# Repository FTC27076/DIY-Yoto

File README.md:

# DIY Yoto

A screen-free, kid-friendly audio player in the style of a Yoto. Put a card on top and it plays that card's stories or songs. It runs fully offline: no Wi-Fi, no app, no account. All audio lives on a micro SD card, and any 13.56 MHz RFID card or NFC sticker can become a card.

## Features

- Tap a card to play, lift it to pause, put it back to resume where it stopped
- Each card remembers which track it was on
- Two knobs: volume (press to pause) and track skip (press to restart the track)
- Volume cap for small ears
- Rechargeable LiPo with USB-C charging; play while charging
- Deep sleep after 5 minutes idle, wake with either knob
- Low-battery warning and safe shutdown

## Hardware

| Part | What it does |
|---|---|
| ESP32-S3-WROOM-1 (SMD) | Main controller |
| RC522 RFID reader | Reads the cards |
| Adafruit MAX98357A (#3006) | I2S amplifier, drives a 4–8 Ω 3 W speaker |
| Adafruit micro SD breakout (#4682) | Audio storage, 4-bit SDIO |
| TP4056 USB-C module (with protection) | Charges and protects the battery |
| MT3608 boost module | 5 V for the amp (set to 5.0 V before connecting!) |
| MCP1825S-3302E/AB (TO-220) | 3.3 V regulator for the logic |
| 2× EC11 rotary encoders | Volume and track controls |
| USB-C (J16) | Programming and Serial Monitor only |
| 3.7 V 2000 mAh LiPo (Adafruit #2011) | Power |

Everything except the ESP32 module is through-hole or a module on headers, so it's hand-solderable.
## BILL OF MATERIALS

Costs are in USD for one player. Most unit prices are estimates, so check them in each cart.

| Item | Qty | Supplier | Cost/item | Total Cost | link |
|---|---:|---|---:|---:|---|
| U2 – ESP32-S3-WROOM-1-N8R8 module (Espressif) | 1 | DigiKey | $4.50 | $4.50 | [link](https://www.digikey.ca/en/products/detail/espressif-systems/ESP32-S3-WROOM-1-N8R8/15295891) |
| U1 – MCP1825S-3302E/AB 3.3V LDO, TO-220 (Microchip) | 1 | DigiKey | $1.75 | $1.75 | [link](https://www.digikey.ca/en/products/result?keywords=MCP1825S-3302E%2FAB) |
| R1, R2 – 100k 1/4W resistor (Stackpole CF14JT100K, cut tape) | 2 | DigiKey | $0.10 | $0.20 | [link](https://www.digikey.ca/en/products/result?keywords=CF14JT100K) |
| R3–R8 – 10k 1/4W resistor (Stackpole CF14JT10K0, cut tape) | 6 | DigiKey | $0.10 | $0.60 | [link](https://www.digikey.ca/en/products/result?keywords=CF14JT10K0) |
| R9, R10 – 5.1k 1/4W resistor (Stackpole CF14JT5K10, cut tape) | 2 | DigiKey | $0.10 | $0.20 | [link](https://www.digikey.ca/en/products/detail/stackpole-electronics-inc/CF14JT5K10/1830367) |
| C1, C5 – 100µF 16V electrolytic (Panasonic EEU-FR1C101) | 2 | DigiKey | $0.40 | $0.80 | [link](https://www.digikey.ca/en/products/detail/panasonic-industry/EEU-FR1C101/2433525) |
| C2, C3, C9 – 10µF 25V ceramic, 5mm pitch (TDK FG28X5R1E106MRT06) | 3 | LCSC / JLC | $0.20 | $0.60 | [link](https://www.lcsc.com/product-detail/C1620216.html) |
| C4, C6, C7, C10 – 100nF 50V ceramic (KNSCHA 178MU0006) | 4 | LCSC / JLC | $0.03 | $0.12 | [link](https://www.lcsc.com/product-detail/C5632430.html) |
| C8 – 1µF 50V ceramic (KNSCHA 178MU0010) | 1 | LCSC / JLC | $0.05 | $0.05 | [link](https://www.lcsc.com/product-detail/C5632434.html) |
| SW2, SW3 – 6x6mm tactile switch, reset/boot (Omron B3F-1000) | 2 | DigiKey | $0.35 | $0.70 | [link](https://www.digikey.ca/en/products/detail/omron-electronics-inc-emc-div/B3F-1000/33150) |
| SW4, SW5 – rotary encoder with switch (Alps EC11E15244G1) | 2 | LCSC / JLC | $1.50 | $3.00 | [link](https://www.lcsc.com/product-detail/C370970.html) |
| J16 – USB-C receptacle, 16-pin (HRO TYPE-C-31-M-12) | 1 | LCSC / JLC | $0.25 | $0.25 | [link](https://www.lcsc.com/product-detail/C165948.html) |
| J3 – JST-PH 2-pin side-entry socket, battery (JST S2B-PH-K-S) | 1 | LCSC / JLC | $0.10 | $0.10 | [link](https://www.lcsc.com/product-detail/C173752.html) |
| J7 – JST-XH 2-pin socket, power switch (JST B2B-XH-A) | 1 | LCSC / JLC | $0.05 | $0.05 | [link](https://www.lcsc.com/product-detail/C158012.html) |
| MOD1 – 1x8 2.54mm female header (BOOMELE) | 1 | LCSC / JLC | $0.10 | $0.10 | [link](https://www.lcsc.com/product-detail/C27438.html) |
| J12 (M1) – TP4056 USB-C charger module with protection (pack of 5) | 1 | Amazon | $8.00 | $8.00 | [link](https://www.amazon.ca/s?k=TP4056+type-c+protection+module) |
| J13 (M2) – MT3608 boost module (pack of 5) | 1 | Amazon | $8.00 | $8.00 | [link](https://www.amazon.ca/s?k=MT3608+boost+module) |
| J14 (M3) – Adafruit MAX98357A I2S amp breakout (3006) | 1 | DigiKey | $5.95 | $5.95 | [link](https://www.digikey.ca/en/products/detail/adafruit-industries-llc/3006/6058477) |
| J15 (M4) – Adafruit micro SD SPI/SDIO breakout (4682) | 1 | DigiKey | $3.50 | $3.50 | [link](https://www.digikey.ca/en/products/detail/adafruit-industries-llc/4682/12822319) |
| MOD1 – RC522 RFID reader kit with card + fob (ProtoSupplies) | 1 | ProtoSupplies | $2.59 | $2.59 | [link](https://protosupplies.com/product/mfrc522-rfid-reader-key-card-and-key-ring/) |
| Header pins for M1/M2 – 1x40 break-away male header (BOOMELE) | 1 | LCSC / JLC | $0.15 | $0.15 | [link](https://www.lcsc.com/product-detail/C2337.html) |
| LiPo battery 3.7V 2000mAh with JST-PH (Adafruit 2011) | 1 | DigiKey | $12.50 | $12.50 | [link](https://www.digikey.ca/en/products/detail/adafruit-industries-llc/2011/6612469) |
| Speaker 40mm 4Ω 3W (Adafruit 3968) | 1 | DigiKey | $4.95 | $4.95 | [link](https://www.digikey.ca/en/products/detail/adafruit-industries-llc/3968/9745251) |
| Power switch – SPDT panel toggle 5A (E-Switch 100SP1T1B1M2QEH) | 1 | DigiKey | $4.50 | $4.50 | [link](https://www.digikey.ca/en/products/detail/e-switch/100SP1T1B1M2QEH/378821) |
| RFID cards – MIFARE Classic 1K (Adafruit 359) | 5 | DigiKey | $1.95 | $9.75 | [link](https://www.digikey.ca/en/products/detail/adafruit-industries-llc/359/5353589) |
| micro SD card 16–32GB (SanDisk / Samsung) | 1 | Amazon | $8.00 | $8.00 | [link](https://www.amazon.ca/s?k=sandisk+32gb+microsd) |
| Optional – JST-XH plug housing for J7 (JST XHP-2) | 0 | DigiKey | $0.10 | $0.00 | [link](https://www.digikey.ca/en/products/detail/jst-sales-america-inc/XHP-2/555485) |
| Optional – JST-XH crimp contacts (JST SXH-001T-P0.6, cut tape) | 0 | DigiKey | $0.10 | $0.00 | [link](https://www.digikey.ca/en/products/detail/jst-sales-america-inc/SXH-001T-P0.6/455-1135-1-ND/527370) |
| Parts subtotal | | | | $80.91 | |
| Tax (Ontario HST 13%) | | | | $13.77 | |
| **Grand total (USD)** | | | | **~$119.68** | |

### Pin map

| Function | GPIO |
|---|---|
| I2S BCLK / LRC / DIN | 5 / 6 / 7 |
| Amp enable (SD_MODE) | 8 |
| RC522 RST / SS / MOSI / SCK / MISO | 9 / 10 / 11 / 12 / 13 |
| SD CMD / CLK / D0 / D1 / D2 / D3 | 14 / 39 / 40 / 41 / 42 / 21 |
| Volume encoder A / B / push | 15 / 16 / 17 |
| Track encoder A / B / push | 18 / 4 / 2 |
| Battery sense (100k/100k divider) | 1 |
| USB D− / D+ | 19 / 20 |

## Repository contents

| Path | What's in it |
|---|---|
| `DiyYoto/DiyYoto.ino` | Arduino firmware |
| `DiyYoto/README.md` | Full firmware setup, SD card layout, controls and troubleshooting |
| `DiyYoto.pretty/` | Custom KiCad footprints for the four modules |
| `make_footprints.py` | Regenerates those footprints |

## Quick start

1. **Build the board.** Order the PCB, solder the parts, and set the MT3608 to 5.0 V with a multimeter *before* plugging in the amp.
2. **Flash the firmware.** In Arduino IDE 2, install the ESP32 core plus the MFRC522 and ESP32-audioI2S libraries. Set Board to *ESP32S3 Dev Module*, USB CDC On Boot to *Enabled*, and PSRAM to match your module. Switch the player on, plug USB into J16, hold BOOT, tap RESET, release BOOT, then upload.
3. **Prepare the SD card.** Format it FAT32 and create a `/cards` folder.
4. **Add a card.** Tap a blank card. The player creates `/cards/<card UID>/`. Copy MP3s into that folder (they play in alphabetical order), put the SD card back, and tap again.

## Images of final design

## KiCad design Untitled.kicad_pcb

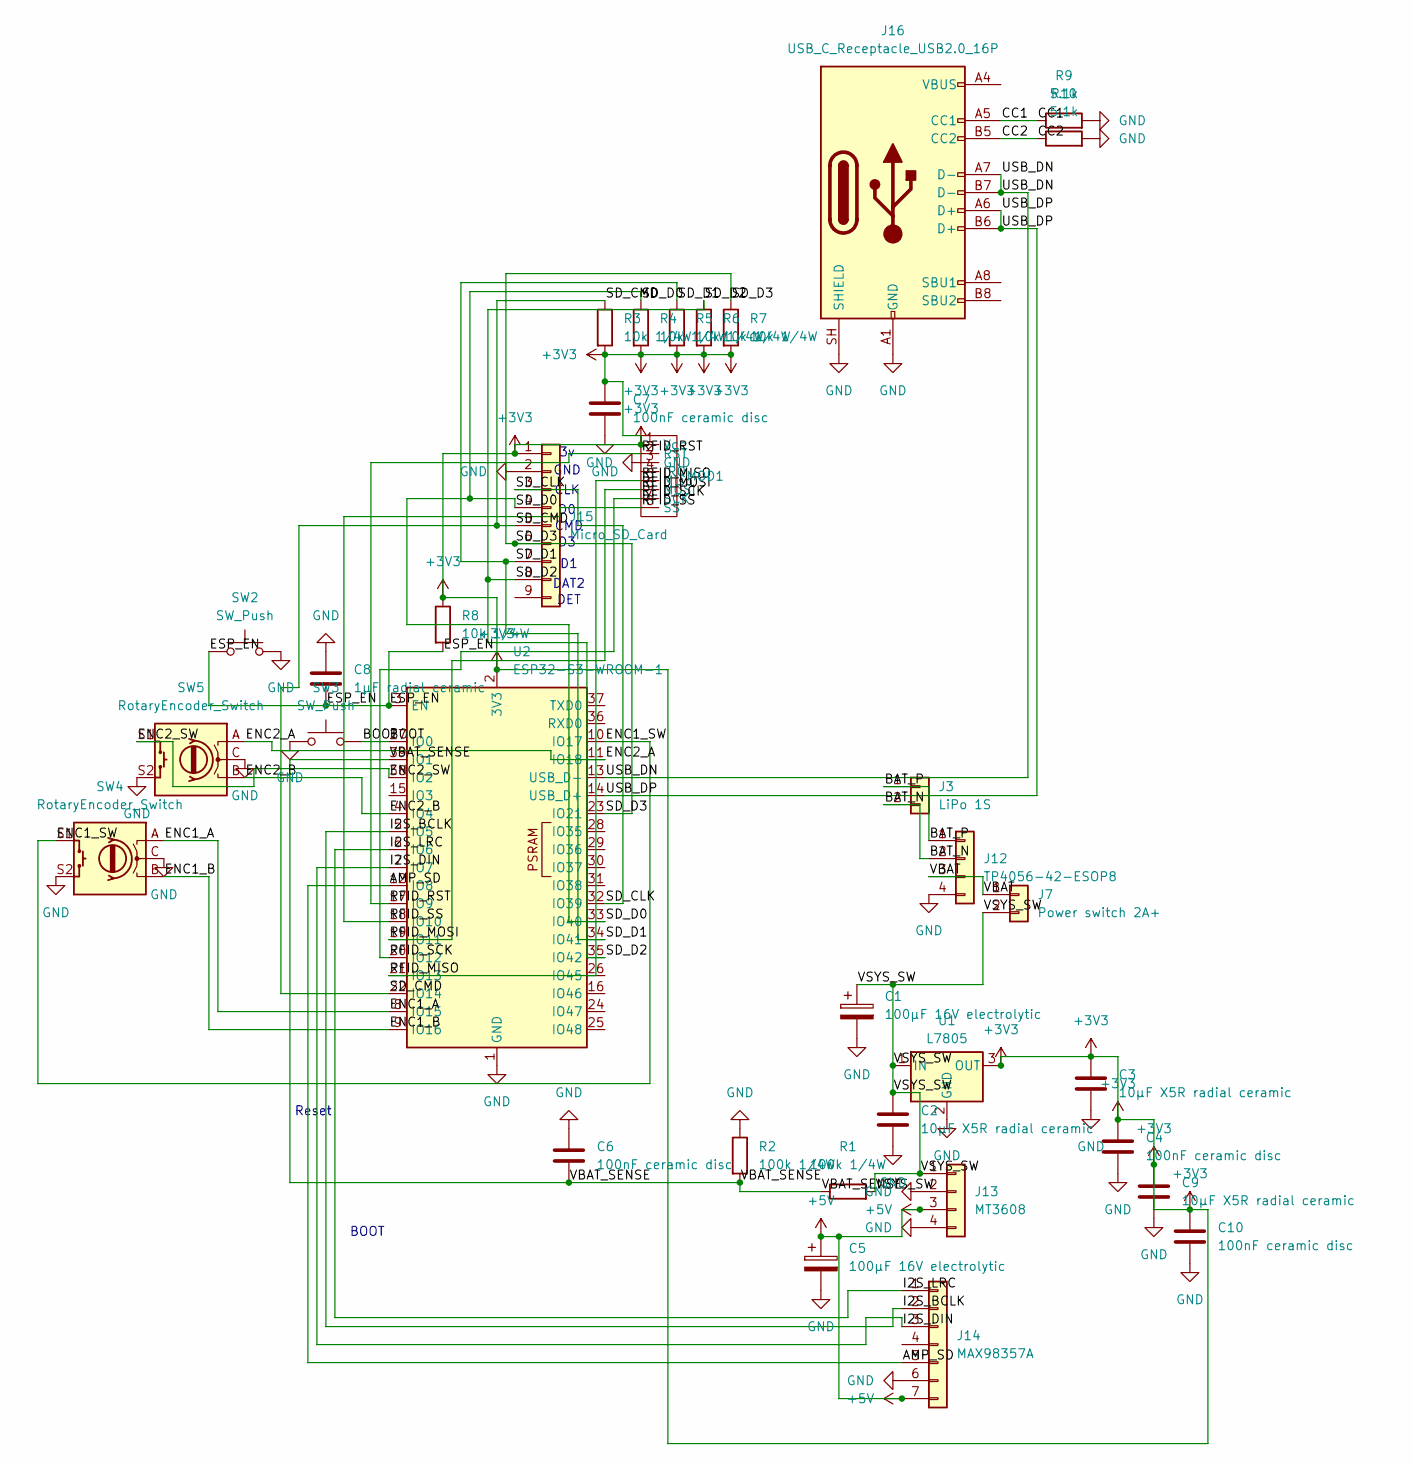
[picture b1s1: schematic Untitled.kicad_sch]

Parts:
C1, C5: 100µF 16V electrolytic; CP_Radial_D6.3mm_P2.50mm
C2, C3, C9: 10µF X5R radial ceramic; C_Disc_D5.0mm_W2.5mm_P2.50mm
C4, C6, C7, C10: 100nF ceramic disc; C_Disc_D3.0mm_W1.6mm_P2.50mm
C8: 1µF radial ceramic; C_Disc_D3.0mm_W1.6mm_P2.50mm
J3: LiPo 1S; JST_PH_S2B-PH-K_1x02_P2.00mm_Horizontal
J7: Power switch 2A+; JST_XH_B2B-XH-A_1x02_P2.50mm_Vertical
J12: TP4056-42-ESOP8; TP4056_USBC_Protected_Module
J13: MT3608; MT3608_Boost_Module
J14: MAX98357A; Adafruit_MAX98357A_3006
J15: Micro_SD_Card; Adafruit_MicroSD_SDIO_4682
J16: USB_C_Receptacle_USB2.0_16P; USB_C_Receptacle_HRO_TYPE-C-31-M-12
MOD1: PinSocket_1x08_P2.54mm_Vertical
R1, R2: 100k 1/4W; R_Axial_DIN0207_L6.3mm_D2.5mm_P10.16mm_Horizontal
R3, R4, R5, R6, R7, R8: 10k 1/4W; R_Axial_DIN0207_L6.3mm_D2.5mm_P10.16mm_Horizontal
R9, R10: 5.1k; R_Axial_DIN0207_L6.3mm_D2.5mm_P10.16mm_Horizontal
SW2, SW3: SW_Push; SW_PUSH_6mm
SW4, SW5: RotaryEncoder_Switch; RotaryEncoder_Alps_EC11E-Switch_Vertical_H20mm_MountingHoles
U1: L7805; TO-220-3_Vertical
U2: ESP32-S3-WROOM-1; ESP32-S3-WROOM-1ThermalVia0.3

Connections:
+3V3: C3.1, C4.1, C7.1, C9.1, C10.1, J15.1, MOD1.1 (Vcc), R3.2, R4.2, R5.2, R6.2, R7.2, R8.1, U1.3 (OUT), U2.2 (3V3)
+5V: C5.1, J13.3, J14.7
/AMP_SD: J14.5, U2.12 (IO8)
/BAT_N: J3.2, J12.2
/BAT_P: J3.1, J12.1
/BOOT: SW3.2, U2.27 (IO0)
/CC1: J16.A5 (CC1), R9.1
/CC2: J16.B5 (CC2), R10.1
/ENC1_A: SW4.A, U2.8 (IO15)
/ENC1_B: SW4.B, U2.9 (IO16)
/ENC1_SW: SW4.S1, U2.10 (IO17)
/ENC2_A: SW5.A, U2.11 (IO18)
/ENC2_B: SW5.B, U2.4 (IO4)
/ENC2_SW: SW5.S1, U2.38 (IO2)
/ESP_EN: C8.2, R8.2, SW2.1, U2.3 (EN)
/I2S_BCLK: J14.2, U2.5 (IO5)
/I2S_DIN: J14.3, U2.7 (IO7)
/I2S_LRC: J14.1, U2.6 (IO6)
/RFID_MISO: MOD1.5 (Miso), U2.21 (IO13)
/RFID_MOSI: MOD1.6 (MOSI), U2.19 (IO11)
/RFID_RST: MOD1.2 (RST), U2.17 (IO9)
/RFID_SCK: MOD1.7 (SCK), U2.20 (IO12)
/RFID_SS: MOD1.8 (SS), U2.18 (IO10)
/SD_CLK: J15.3, U2.32 (IO39)
/SD_CMD: J15.5, R3.1, U2.22 (IO14)
/SD_D0: J15.4, R4.1, U2.33 (IO40)
/SD_D1: J15.7, R5.1, U2.34 (IO41)
/SD_D2: J15.8, R6.1, U2.35 (IO42)
/SD_D3: J15.6, R7.1, U2.23 (IO21)
/USB_DN: J16.A7 (D-), J16.B7 (D-), U2.13 (USB_D-)
/USB_DP: J16.A6 (D+), J16.B6 (D+), U2.14 (USB_D+)
/VBAT: J7.1, J12.3
/VBAT_SENSE: C6.2, R1.1, R2.2, U2.39 (IO1)
/VSYS_SW: C1.1, C2.1, J7.2, J13.1, R1.2, U1.1 (IN)
GND: C1.2, C2.2, C3.2, C4.2, C5.2, C6.1, C7.2, C8.1, C9.2, C10.2, J12.4, J13.2, J13.4, J14.6, J15.2, J16.A1 (GND), J16.A12 (GND), J16.B1 (GND), J16.B12 (GND), J16.SH (SHIELD), MOD1.3 (GND), R2.1, R9.2, R10.2, SW2.2, SW3.1, SW4.C, SW4.S2, SW5.C, SW5.S2, U1.2 (GND), U2.1 (GND), U2.40 (GND), U2.41 (GND)
unnamed: J16.A4 (VBUS), J16.A9 (VBUS), J16.B4 (VBUS), J16.B9 (VBUS)

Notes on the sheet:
Reset
BOOT
DAT2
GND
CMD
CLK
DET

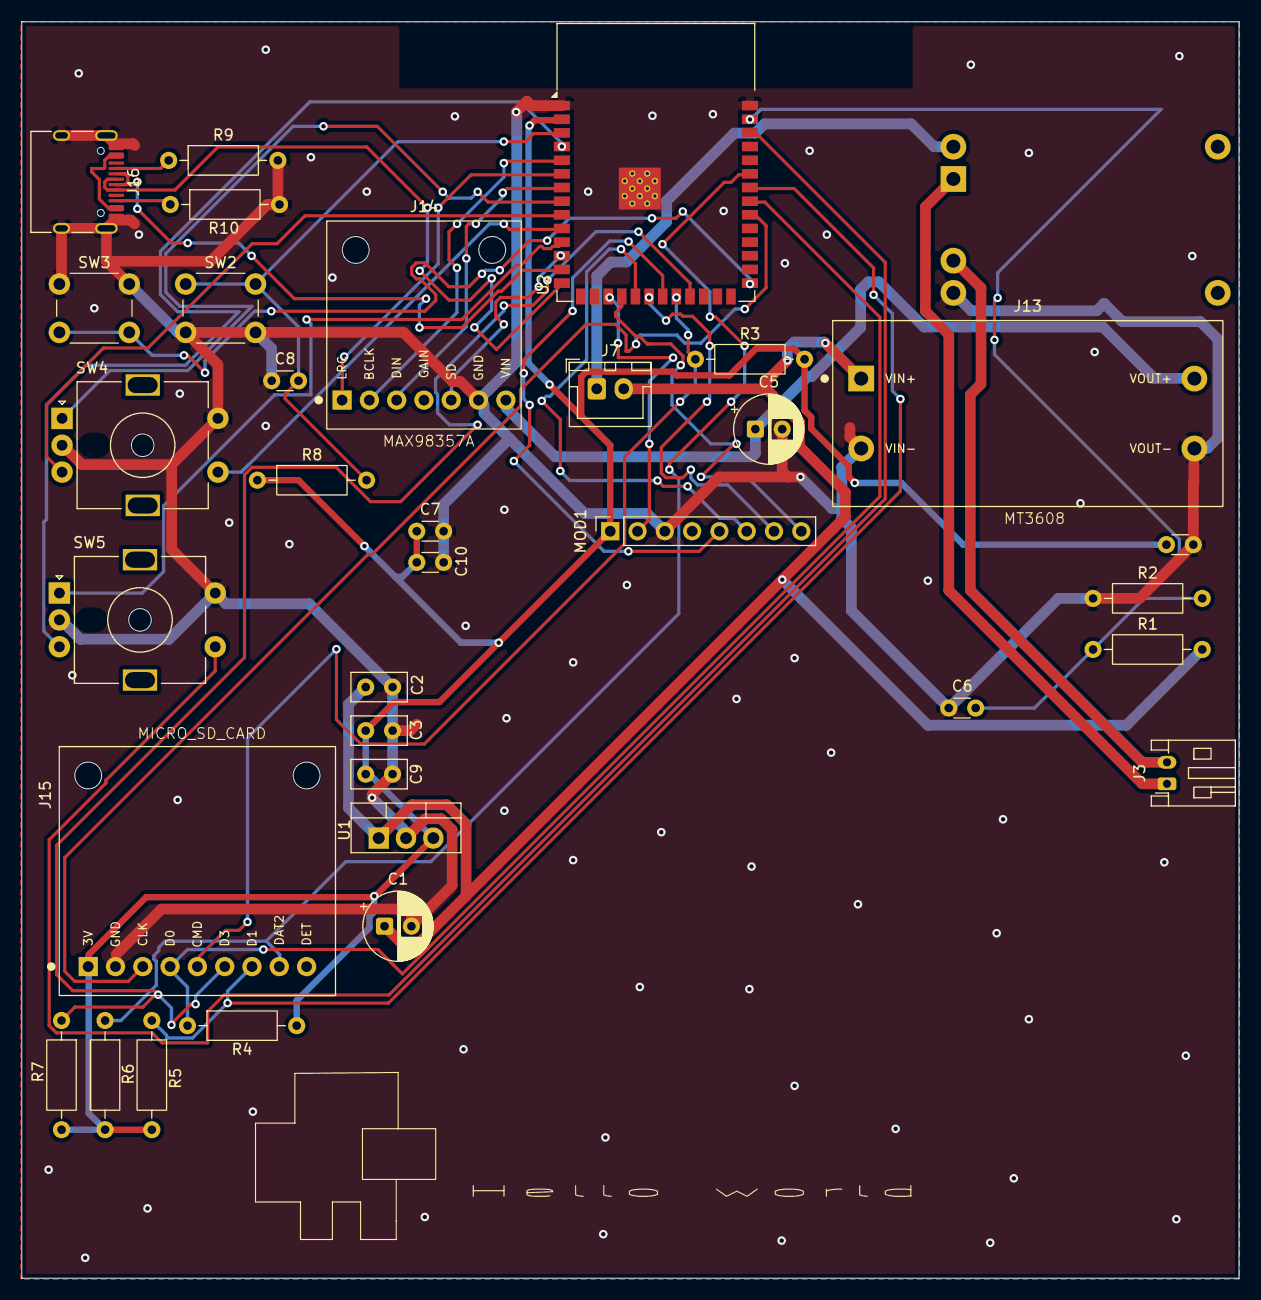
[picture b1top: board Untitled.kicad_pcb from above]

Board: 2 copper layers, 113.2 x 116.9 mm, 34 parts (1 on the bottom side), 36 nets.

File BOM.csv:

Item,Qty,Supplier,Cost/item,Total Cost,link
U2 – ESP32-S3-WROOM-1-N8R8 module (Espressif),1,DigiKey,$4.50,$4.50,https://www.digikey.ca/en/products/detail/espressif-systems/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
"U1 – MCP1825S-3302E/AB 3.3V LDO, TO-220 (Microchip)",1,DigiKey,$1.75,$1.75,https://www.digikey.ca/en/products/result?keywords=MCP1825S-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
"R1, R2 – 100k 1/4W resistor (Stackpole CF14JT100K, cut tape)",2,DigiKey,$0.10,$0.20,https://www.digikey.ca/en/products/result?keywords=CF14JT100K
"R3–R8 – 10k 1/4W resistor (Stackpole CF14JT10K0, cut tape)",6,DigiKey,$0.10,$0.60,https://www.digikey.ca/en/products/result?keywords=CF14JT10K0
"R9, R10 – 5.1k 1/4W resistor (Stackpole CF14JT5K10, cut tape)",2,DigiKey,$0.10,$0.20,https://www.digikey.ca/en/products/detail/stackpole-electron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
"C1, C5 – 100µF 16V electrolytic (Panasonic EEU-FR1C101)",2,DigiKey,$0.40,$0.80,https://www.digikey.ca/en/products/detail/panasonic-industry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
"C2, C3, C9 – 10µF 25V ceramic, 5mm pitch (TDK FG28X5R1E106MRT06)",3,LCSC / JLC,$0.20,$0.60,https://www.lcsc.com/product-detail/C1620216.html
"C4, C6, C7, C10 – 100nF 50V ceramic (KNSCHA 178MU0006)",4,LCSC / JLC,$0.03,$0.12,https://www.lcsc.com/product-detail/C5632430.html
C8 – 1µF 50V ceramic (KNSCHA 178MU0010),1,LCSC / JLC,$0.05,$0.05,https://www.lcsc.com/product-detail/C5632434.html
"SW2, SW3 – 6x6mm tactile switch, reset/boot (Omron B3F-1000)",2,DigiKey,$0.35,$0.70,https://www.digikey.ca/en/products/detail/omron-electronics-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
"SW4, SW5 – rotary encoder with switch (Alps EC11E15244G1)",2,LCSC / JLC,$1.50,$3.00,https://www.lcsc.com/product-detail/C370970.html
"J16 – USB-C receptacle, 16-pin (HRO TYPE-C-31-M-12)",1,LCSC / JLC,$0.25,$0.25,https://www.lcsc.com/product-detail/C165948.html
"J3 – JST-PH 2-pin side-entry socket, battery (JST S2B-PH-K-S)",1,LCSC / JLC,$0.10,$0.10,https://www.lcsc.com/product-detail/C173752.html
"J7 – JST-XH 2-pin socket, power switch (JST B2B-XH-A)",1,LCSC / JLC,$0.05,$0.05,https://www.lcsc.com/product-detail/C158012.html
MOD1 – 1x8 2.54mm female header (BOOMELE),1,LCSC / JLC,$0.10,$0.10,https://www.lcsc.com/product-detail/C27438.html
J12 (M1) – TP4056 USB-C charger module with protection (pack of 5),1,Amazon,$8.00,$8.00,https://www.amazon.ca/s?k=TP4056+type-c+protection+module
J13 (M2) – MT3608 boost module (pack of 5),1,Amazon,$8.00,$8.00,https://www.amazon.ca/s?k=MT3608+boost+module
J14 (M3) – Adafruit MAX98357A I2S amp breakout (3006),1,DigiKey,$5.95,$5.95,https://www.digikey.ca/en/products/detail/adafruit-industrie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
J15 (M4) – Adafruit micro SD SPI/SDIO breakout (4682),1,DigiKey,$3.50,$3.50,https://www.digikey.ca/en/products/detail/adafruit-industrie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
MOD1 – RC522 RFID reader kit with card + fob (ProtoSupplies),1,ProtoSupplies,$2.59,$2.59,https://protosupplies.com/product/mfrc522-rfid-reader-key-ca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
Header pins for M1/M2 – 1x40 break-away male header (BOOMELE),1,LCSC / JLC,$0.15,$0.15,https://www.lcsc.com/product-detail/C2337.html
LiPo battery 3.7V 2000mAh with JST-PH (Adafruit 2011),1,DigiKey,$12.50,$12.50,https://www.digikey.ca/en/products/detail/adafruit-industrie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
Speaker 40mm 4Ω 3W (Adafruit 3968),1,DigiKey,$4.95,$4.95,https://www.digikey.ca/en/products/detail/adafruit-industrie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
Power switch – SPDT panel toggle 5A (E-Switch 100SP1T1B1M2QEH),1,DigiKey,$4.50,$4.50,https://www.digikey.ca/en/products/detail/e-switch/100SP1T1B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
Estimated total shipping,1,,,$38.77,

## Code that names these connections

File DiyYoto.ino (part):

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#include "soc/gpio_reg.h"

// ===================== Pins (match the schematic) =====================
constexpr int PIN_I2S_BCLK  = 5;
constexpr int PIN_I2S_LRC   = 6;
constexpr int PIN_I2S_DOUT  = 7;
constexpr int PIN_AMP_SD    = 8;    // MAX98357A SD_MODE: HIGH = on, LOW = shutdown

constexpr int PIN_RFID_RST  = 9;
constexpr int PIN_RFID_SS   = 10;
constexpr int PIN_RFID_MOSI = 11;
constexpr int PIN_RFID_SCK  = 12;
constexpr int PIN_RFID_MISO = 13;

constexpr int PIN_SD_CMD    = 38;
constexpr int PIN_SD_CLK    = 39;
constexpr int PIN_SD_D0     = 40;
constexpr int PIN_SD_D1     = 41;
constexpr int PIN_SD_D2     = 42;
constexpr int PIN_SD_D3     = 21;

constexpr int PIN_VOL_A     = 15;
constexpr int PIN_VOL_B     = 16;
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
// ===================== Globals =====================
Audio       audio;
MFRC522     rfid(PIN_RFID_SS, PIN_RFID_RST);
Preferences prefs;

enum class State { Idle, Playing, Paused, CardRemoved, SystemSound };
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}

// ===================== Helpers =====================
void ampOn()  { digitalWrite(PIN_AMP_SD, HIGH); }
void ampOff() { digitalWrite(PIN_AMP_SD, LOW); }

String trackKey(const String& uid) {
  // Preferences keys max 15 chars
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  Serial.println("Going to sleep. Press a knob to wake.");
  audio.stopSong();
  ampOff();
  digitalWrite(PIN_RFID_RST, LOW);  // RC522 hard power-down
  gpio_hold_en((gpio_num_t)PIN_RFID_RST);
  gpio_hold_en((gpio_num_t)PIN_AMP_SD);
  gpio_deep_sleep_hold_en();

  rtc_gpio_pullup_en((gpio_num_t)PIN_BTN_VOL);
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  Serial.println("\nDIY Yoto starting (offline mode)");

  // Undo anything left over from deep sleep
  gpio_hold_dis((gpio_num_t)PIN_RFID_RST);
  gpio_hold_dis((gpio_num_t)PIN_AMP_SD);
  gpio_deep_sleep_hold_dis();
  rtc_gpio_deinit((gpio_num_t)PIN_BTN_VOL);
  rtc_gpio_deinit((gpio_num_t)PIN_BTN_TRK);

  pinMode(PIN_AMP_SD, OUTPUT);
  ampOff();
  pinMode(PIN_BTN_VOL, INPUT_PULLUP);
  pinMode(PIN_BTN_TRK, INPUT_PULLUP);
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  volume = constrain(prefs.getInt("vol", START_VOLUME), 0, MAX_VOLUME);

  // SD card in 4-bit SDMMC mode
  SD_MMC.setPins(PIN_SD_CLK, PIN_SD_CMD, PIN_SD_D0, PIN_SD_D1, PIN_SD_D2, PIN_SD_D3);
  while (!SD_MMC.begin("/sdcard", false)) {
    Serial.println("SD card not found - insert a FAT32 card. Retrying...");
    delay(2000);
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  Serial.printf("SD card OK (%llu MB)\n", SD_MMC.cardSize() / (1024ULL * 1024ULL));

  // RFID
  SPI.begin(PIN_RFID_SCK, PIN_RFID_MISO, PIN_RFID_MOSI, PIN_RFID_SS);
  rfid.PCD_Init();
  rfid.PCD_SetAntennaGain(rfid.RxGain_max);
  byte ver = rfid.PCD_ReadRegister(MFRC522::VersionReg);
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                (ver == 0x00 || ver == 0xFF) ? "(not responding - check wiring!)" : "");

  // Audio
  audio.setPinout(PIN_I2S_BCLK, PIN_I2S_LRC, PIN_I2S_DOUT);
  audio.forceMono(true);  // single speaker: mix left + right
  audio.setVolume(volume);

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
